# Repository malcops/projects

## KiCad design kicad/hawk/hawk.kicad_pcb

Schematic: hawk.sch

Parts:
C1: 0.1uf; C_0805_2012Metric_Pad1.15x1.40mm_HandSolder
C2, C3: 1uF; C_0805_2012Metric_Pad1.15x1.40mm_HandSolder
D1: LED_ALT; LED_0805_2012Metric_Pad1.15x1.40mm_HandSolder
J1: GPIO_AA; PinHeader_1x05_P2.54mm_Vertical
J2: GPIO_BB; PinHeader_1x05_P2.54mm_Vertical
J3: SWD_PGM; PinHeader_2x03_P2.54mm_Vertical
J4: Battery; JST_PH_B2B-PH-K_1x02_P2.00mm_Vertical
R1: 10k; R_0805_2012Metric_Pad1.15x1.40mm_HandSolder
R2, R3: 1k; R_0805_2012Metric_Pad1.15x1.40mm_HandSolder
SW1: SW_Push; SW_PUSH_6mm
U1: ATSAMD10C14A-SS; SOIC-14_3.9x8.7mm_P1.27mm
U2: AP7333-33SRG-7; SOT-23

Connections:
+3V3: C1.1, C3.1, J2.4, J3.2, R1.1, R3.1, U1.12 (VDD), U2.2
+BATT: C2.1, J4.1, U2.3
GND: C1.2, C2.2, C3.2, J2.3, J3.6, J4.2, R2.1, SW1.2, U1.11 (GND)
GPIO_1: J1.2, U1.2 (PA08/XIN)
GPIO_2: J1.3, U1.3 (PA09/XOUT)
GPIO_3: J2.5, U1.14 (PA04)
GPIO_4: J1.1, U1.1 (PA05)
GPIO_5: J1.4, U1.4 (PA14)
GPIO_6: J1.5, U1.5 (PA15)
GPIO_7: J2.1, U1.9 (PA24)
GPIO_8: J2.2, U1.10 (PA25)
LED: D1.2 (A), U1.13 (PA02)
unnamed: D1.1 (K), R2.2
SWCLK: J3.3, R3.2, U1.7 (PA30/SWCLK)
SWDIO: J3.1, U1.8 (PA31/SWDIO)
reset: J3.5, R1.2, SW1.1, U1.6 (PA28/~RST)

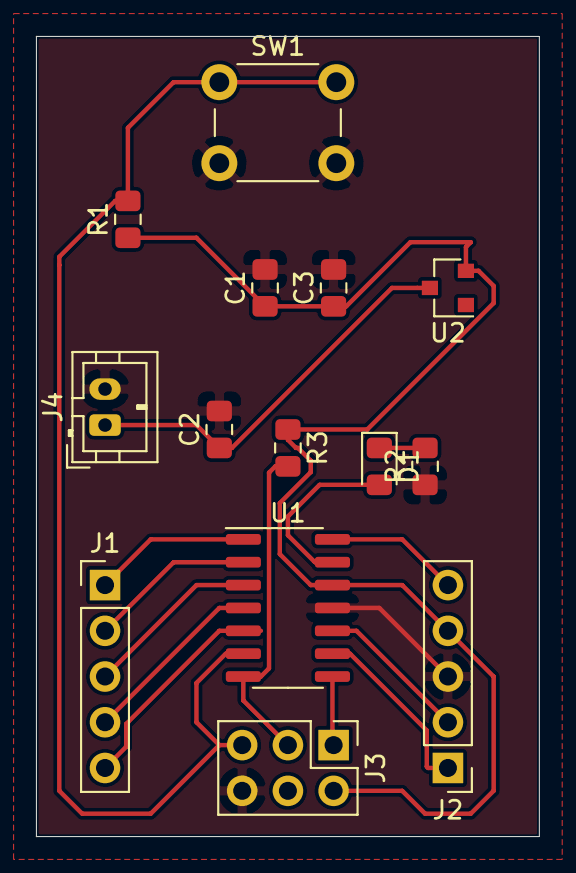
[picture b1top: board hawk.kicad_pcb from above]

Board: 2 copper layers, 27.9 x 44.4 mm, 14 parts (0 on the bottom side), 16 nets.

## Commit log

2019-07-08 Initial zeromq files
2019-08-02 Challenge - Celsius to Farenheit temperature conversion
2019-08-07 Challenge - Marginal tax calculations
2019-08-15 Challenge - Fibonacci numbers
2019-08-22 Challenge - Magic squares
2019-09-28 requirements.txt for python virtualenv
2019-09-28 Challenge - utility to retrieve Linux sysinfo
2020-02-17 Challenge - blink Thinkpad LEDs
2020-05-06 Add libzmq to Dockerfile
2020-05-06 Add initial Dockerfile for repository
2020-05-25 Add googletest to Dockerfile
2020-07-05 Nand2Tetris Week 01
2020-07-05 Nand2Tetris Week 03
2020-07-05 Nand2Tetris Week 04
2020-07-05 Nand2Tetris Week 00
2020-07-05 Nand2Tetris Week 02
2020-07-05 Nand2Tetris Week 06
2020-07-05 Nand2Tetris Week 05
2020-10-14 Example folder setup to run GoogleTest
2020-10-19 Add small_programs Makefile
2020-10-19 Interface to MPU6050, with unit tests (googletest)
2020-10-21 Add MPU6050 temperature sensor
2020-10-21 fixup! Interface to MPU6050, with unit tests (googletest)
2020-11-07 GoPro Session 5 API in C++ v1.0
2020-11-10 fixup! GoPro Session 5 API in C++ v1.0
2020-11-23 Move IMU file to mpu6050 folder
2020-11-23 Create MPU6050 class
2020-11-23 fixup! Create MPU6050 class
2020-11-23 rename to MPU6050.*
2020-11-23 fixup! rename to MPU6050.*
2020-11-25 Updated .gitignore throughout repository
2020-11-25 GoPro API v2.0
2020-11-25 HW Integration tests, primary and submode std::map
2020-11-26 Initial project-euler/python folder
2020-12-04 Advent of Code - Day 2
2020-12-04 Advent of Code - Day 1
2020-12-04 Advent of Code - Day 3
2020-12-04 Advent of Code - Day 4
2020-12-13 Advent of Code - Day 6
2020-12-13 Advent of Code - Day 9
2020-12-13 Advent of Code - Day 7
2020-12-13 Advent of Code - Day 8
2020-12-13 Advent of Code - Day 5
2020-12-13 Advent of Code - Day 10
2020-12-13 Advent of Code - Day 11
2020-12-13 Advent of Code - Day 13
2020-12-13 Advent of Code - Day 12
2020-12-15 Advent of Code - Day 14
2020-12-15 Advent of Code - Day 15
2020-12-15 working part 2?
2020-12-15 fixup! working part 2?
2020-12-15 fixup! fixup! working part 2?
2020-12-16 Advent of Code - Day 16
2020-12-16 Day 16 - part 2 - one iteration
2020-12-16 part 2 - 2 iterations
2020-12-16 part 2 - general solution
2020-12-16 fixup! part 2 - general solution
2020-12-17 Advent of Code - Day 17
2020-12-17 fixup! Advent of Code - Day 17
2020-12-18 Advent of Code - Day 18
2020-12-18 fixup! Advent of Code - Day 18
2020-12-18 fixup! fixup! Advent of Code - Day 18
2020-12-18 Alternate day17
2020-12-19 Working example, part one incorrect answer
2020-12-19 fixup! Working example, part one incorrect answer
2020-12-19 fixup! fixup! Working example, part one incorrect answer
2020-12-19 day17 working
2020-12-19 remove old day17
2020-12-19 Finished day17.py
2020-12-19 Advent of Code - Day 19
2020-12-19 working examples.. part 1 timeout
2020-12-21 Advent of Code - Day 21
2020-12-21 fixup! Advent of Code - Day 21
2020-12-21 fixup! fixup! Advent of Code - Day 21
2020-12-21 fixup! fixup! fixup! Advent of Code - Day 21
2020-12-21 fixup! fixup! fixup! fixup! Advent of Code - Day 21
2020-12-21 fixup! working examples.. part 1 timeout
2020-12-29 Advent of Code - Day 22
2020-12-29 Advent of Code - template
2020-12-29 fixup! Advent of Code - Day 22
2020-12-30 fixup! fixup! Advent of Code - Day 22
2020-12-30 fixup! fixup! fixup! Advent of Code - Day 22
2021-01-12 Advent of Code - Day 20 (Part 2)
2021-01-12 Advent of Code - Day 24 (Part 2)
2021-01-12 Advent of Code - Day 23
2021-01-12 Advent of Code - Day 20 (Part 1)
2021-01-12 Advent of Code - Day 25 (Part 1)
2021-01-12 Advent of Code - Day 24 (Part 1)
2021-01-13 Advent of Code - Move 2020 code to 2020/ folder
2021-01-21 Advent of Code 2019 - Day 1
2021-01-21 Advent of Code 2019 - Day 2
2021-01-21 Advent of Code 2019 - Day 3
2021-03-01 GoPro - add command for voice control
2021-03-02 GoPro - Add functionality for media refresh, download, and delete
2021-03-10 [ROSALIND] RNA
2021-03-10 [ROSALIND] REVC
2021-03-10 [ROSALIND] DNA
2021-03-10 [ROSALIND] Makefile
2021-03-11 [ROSALIND] GC
2021-03-12 [ROSALIND] HAMM
2021-03-13 [ROSALIND] PROT
2021-03-14 [ROSALIND] PRTM
2021-03-16 [ROSALIND] FIB
2021-03-17 [ROSALIND] PERM
2021-03-18 [ROSALIND] IPRB
2021-03-19 [KICAD] Hawk tutorial pt. 1
2021-03-19 [KICAD] Hawk tutorial pt. 3
2021-03-19 [KICAD] Hawk tutorial pt. 5-8
2021-03-19 [KICAD] Hawk tutorial pt. 4
2021-03-19 [KICAD] Hawk tutorial pt. 2
2021-03-19 [KICAD] Hawk tutorial pt. 9-End
2021-03-20 [KICAD] Basic ngspice example
2021-03-23 [KICAD] ngspice-example2 - BJT
2021-03-24 Initial cmoy schematic using pspice op-amp
2022-11-01 [GOLANG] finance.go to calculate theoretical portfolio
2023-01-05 initial module init
2023-01-05 golfcourse data struct
2023-01-05 scoringrecord data struct
2023-01-21 [UPDATE] finance.go handle errors when run offline
